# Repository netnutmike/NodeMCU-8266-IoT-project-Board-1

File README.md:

# NodeMCU-8266-IoT-project-Board-1
This is a board designed around the NodeMCU8266 with lots of io for IoT projects

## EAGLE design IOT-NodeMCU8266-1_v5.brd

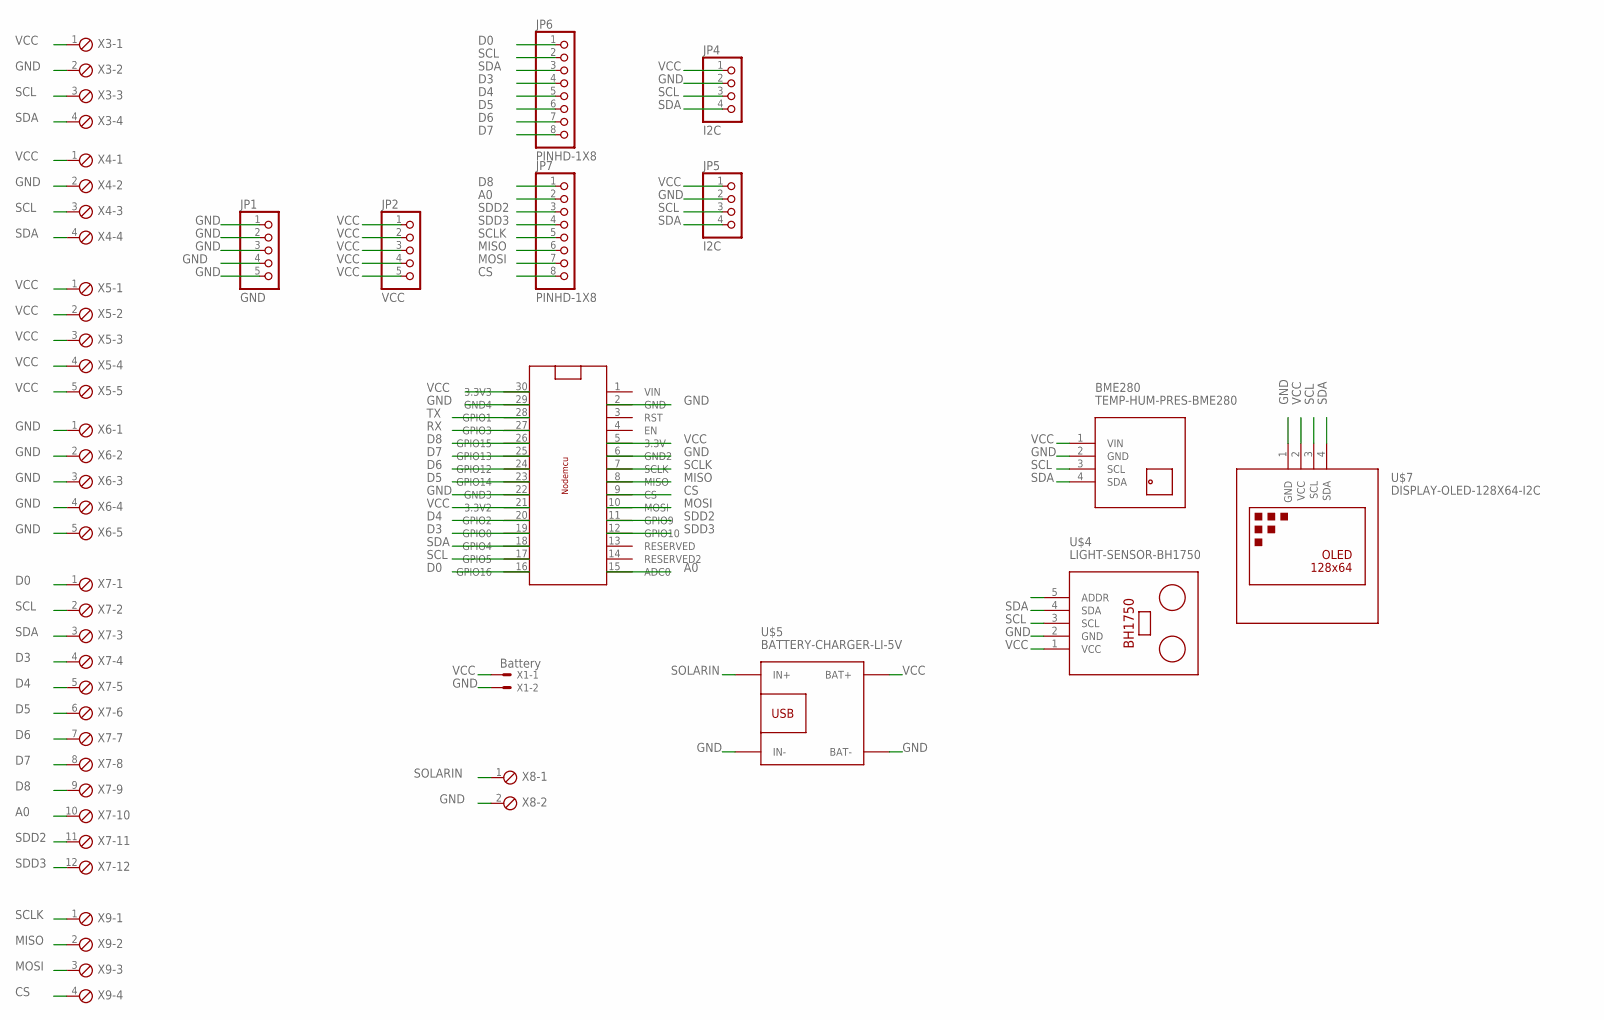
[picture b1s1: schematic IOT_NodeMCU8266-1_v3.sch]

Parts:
BME280: TEMP-HUM-PRES-BME280
JP1: GND; 1X05
JP2: VCC; 1X05
JP4, JP5: I2C; 1X04
JP6, JP7: PINHD-1X8; 1X08
U$1: NODEMCUESP8266
U$4: LIGHT-SENSOR-BH1750
U$5: BATTERY-CHARGER-LI-5V
U$7: DISPLAY-OLED-128X64-I2C
X1: Battery; 53047-02
X3, X4, X9: MPT4; 4POL254
X5, X6: MPT5; 5POL254
X7: MPT12; 12POL254
X8: MPT2; 2POL254

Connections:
A0: JP7.2, U$1.15 (ADC0), X7.10
CS: JP7.8, U$1.9 (CS), X9.4
D0: JP6.1, U$1.16 (GPIO16), X7.1
D3: JP6.4, U$1.19 (GPIO0), X7.4
D4: JP6.5, U$1.20 (GPIO2), X7.5
D5: JP6.6, U$1.23 (GPIO14), X7.6
D6: JP6.7, U$1.24 (GPIO12), X7.7
D7: JP6.8, U$1.25 (GPIO13), X7.8
D8: JP7.1, U$1.26 (GPIO15), X7.9
GND: BME280.2 (GND), JP1.1, JP1.2, JP1.3, JP1.4, JP1.5, JP4.2, JP5.2, U$1.2 (GND), U$1.6 (GND2), U$1.22 (GND3), U$1.29 (GND4), U$4.2 (GND), U$5.BAT-, U$5.IN-, U$7.1 (GND), X1.2, X3.2, X4.2, X6.1, X6.2, X6.3, X6.4, X6.5, X8.2
MISO: JP7.6, U$1.8 (MISO), X9.2
MOSI: JP7.7, U$1.10 (MOSI), X9.3
RX: U$1.27 (GPIO3)
SCL: BME280.3 (SCL), JP4.3, JP5.3, JP6.2, U$1.17 (GPIO5), U$4.3 (SCL), U$7.3 (SCL), X3.3, X4.3, X7.2
SCLK: JP7.5, U$1.7 (SCLK), X9.1
SDA: BME280.4 (SDA), JP4.4, JP5.4, JP6.3, U$1.18 (GPIO4), U$4.4 (SDA), U$7.4 (SDA), X3.4, X4.4, X7.3
SDD2: JP7.3, U$1.11 (GPIO9), X7.11
SDD3: JP7.4, U$1.12 (GPIO10), X7.12
SOLARIN: U$5.IN+, X8.1
TX: U$1.28 (GPIO1)
VCC: BME280.1 (VIN), JP2.1, JP2.2, JP2.3, JP2.4, JP2.5, JP4.1, JP5.1, U$1.5 (3.3V), U$1.21 (3.3V2), U$1.30 (3.3V3), U$4.1 (VCC), U$5.BAT+, U$7.2 (VCC), X1.1, X3.1, X4.1, X5.1, X5.2, X5.3, X5.4, X5.5

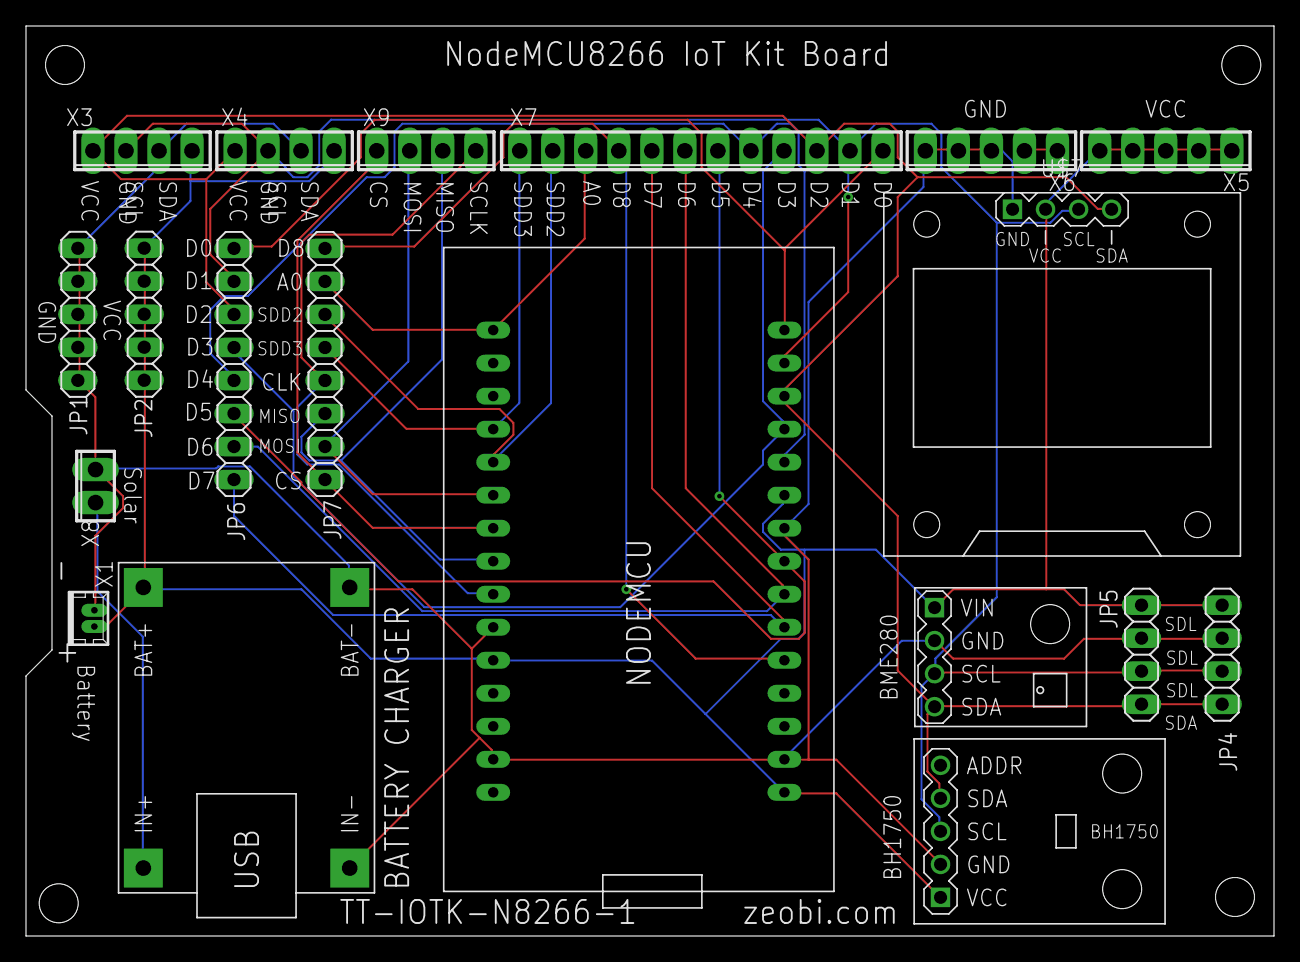
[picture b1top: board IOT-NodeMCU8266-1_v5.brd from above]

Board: 2 copper layers, 96.0 x 70.0 mm, 19 parts (0 on the bottom side), 19 nets.

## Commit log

2021-01-22 initial load

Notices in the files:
parts and their libraries:
diy-modules: Released under the Creative Commons Attribution 4.0 International License: http://creativecommons.org/licenses/by/4.0
